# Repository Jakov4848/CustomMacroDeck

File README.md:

# MACRODECK

<!-- Add a photo of your finished Macropad here -->

This repository contains the hardware and software files for an open-source, programmable macropad keyboard based on the Arduino platform. Developed as a bachelor's thesis, this device allows users to store keyboard shortcuts directly on the hardware's memory, eliminating the need for complex PC software while improving daily workflow productivity.

## Features

- **Native USB HID Emulation:** Powered by an ATmega32U4 microcontroller with an integrated USB controller, meaning it works plug-and-play on any computer without extra drivers.
- **Mechanical Switch Matrix:** Features a 12-key grid with anti-ghosting diodes to prevent false key presses.
- **Hot-Swappable:** Utilizes hot-swap sockets for effortless mechanical switch replacement and testing.
- **Customizable RGB Lighting:** Addressable WS2812B NeoPixel LEDs provide per-key illumination with customizable static colors and dynamic effects.
- **On-Device Interface:** An integrated 0.96" I2C OLED display (SSD1306) and a rotary encoder allow users to navigate menus, select layers, and adjust PC volume directly from the device.
- **Persistent Memory:** Key bindings, macro steps, and layer names are permanently saved in the MCU's 1KB EEPROM.
- **Custom Real-Time Configuration Protocol:** Shortcuts can be reprogrammed in real-time via a serial UART interface using the Arduino IDE Serial Monitor or a Python script.
- **Custom Enclosure:** Designed with a 4-layer laser-cut acrylic (plexiglass) case.

---

## Hardware Bill of Materials (BOM)

The custom PCB was designed in KiCad. If you are assembling the board yourself, you will need the following components:

| Component                  | Description / Package                                            | Quantity |
| :------------------------- | :--------------------------------------------------------------- | :------- |
| **Microcontroller**        | ATmega32U4-AU (QFP-44 10x10)                                     | 1        |
| **USB Connector**          | USB 2.0 Type-C Receptacle 16-pin (SMD)                           | 1        |
| **Display**                | 0.96" OLED I2C SSD1306 (30x30)                                   | 1        |
| **Rotary Encoder**         | EC11 Rotary Switch (THT)                                         | 1        |
| **Mechanical Switches**    | Cherry MX Keyswitches (THT)                                      | 12       |
| **Hot-Swap Sockets**       | CPG151101S11-2 (SMD)                                             | 12       |
| **RGB Lighting LEDs**      | WS2812B NeoPixel LEDs                                            | 12       |
| **Anti-Ghosting Diodes**   | 1N4148W 75V 150mA (SOD-123)                                      | 12       |
| **Reset Switch**           | Tactile Switch 6.1x3.6mm (TS-1092S-B3D2-G)                       | 1        |
| **Crystal Oscillator**     | 16.000MHz SMD5032-2P (ABM3-16.000MHZ-D2Y-T)                      | 1        |
| **Protection**             | Schottky Diode 20V 500mA (MBR0520LT1G)                           | 1        |
| **Protection**             | Polymeric PTC Resettable Fuse 6V 500mA (SMD1206P050TF)           | 1        |
| **LED (Indication)**       | Blue 460nm LED (0603)                                            | 1        |
| **Resistors (0603)**       | 1kΩ (x1), 2.2kΩ (x2), 5.1kΩ (x2), 10kΩ (x2), 470Ω (x2), 22Ω (x2) | 11 Total |
| **Capacitors (0603/0805)** | 100nF (x6), 10uF (x1), 1uF (x1), 22pF (x2)                       | 10 Total |

---

## Building & Installation

1. **PCB & Enclosure:** The PCB manufacturing files are generated from KiCad. The enclosure is constructed from 4 layers of laser-cut black plexiglass.
2. **Bootloader:** A `USBasp` programmer is required to flash the initial bootloader to the ATmega32U4 chip using the ISP (In-System Programming) header.
3. **Firmware:** The firmware is written using the Arduino IDE. Once the bootloader is installed, you can flash updates directly via the USB-C port.

---

## Interface

The macropad operates on a Finite-State Machine with 8 distinct modes (states):

1. **NORMAL:** The primary working state. Scans for keypresses to execute macros and uses the rotary encoder to control PC volume.
2. **MAIN MENU:** Accessed by pressing the rotary encoder button. Allows navigation to other settings.
3. **LAYERS MENU:** Switch between different shortcut layers.
4. **LEDS MENU:** Access sub-menus for lighting.
5. **BRIGHTNESS MENU:** Adjust the intensity of the LED backlights.
6. **STATIC COLORS MENU:** Select a solid color for the keys.
7. **EFFECTS MENU:** Select dynamic RGB animations.
8. **PROG MODE (Programming):** Put the device into configuration mode to remap keys and rename layers via UART.

### Configuration Protocol (How to program macros?)

When the device is in `PROG MODE`, open the Arduino IDE Serial Monitor (or use a serial Python script) to send UART commands. Due to the 1KB EEPROM limit, each macro is restricted to a maximum of 10 sequential keystrokes.

- **To rename a layer**, send:
  `{{layer_id, layer_name}}`
- **To assign a shortcut to a key**, send:
  `<<layer_id, key_id, label, macro_steps>>`
- **To list all current shortcuts**, send:
  `?`

Whenever a programmed key is pressed in normal mode, a pop-up appears on the OLED display showing the executed shortcut (e.g., `CTRL+F`).

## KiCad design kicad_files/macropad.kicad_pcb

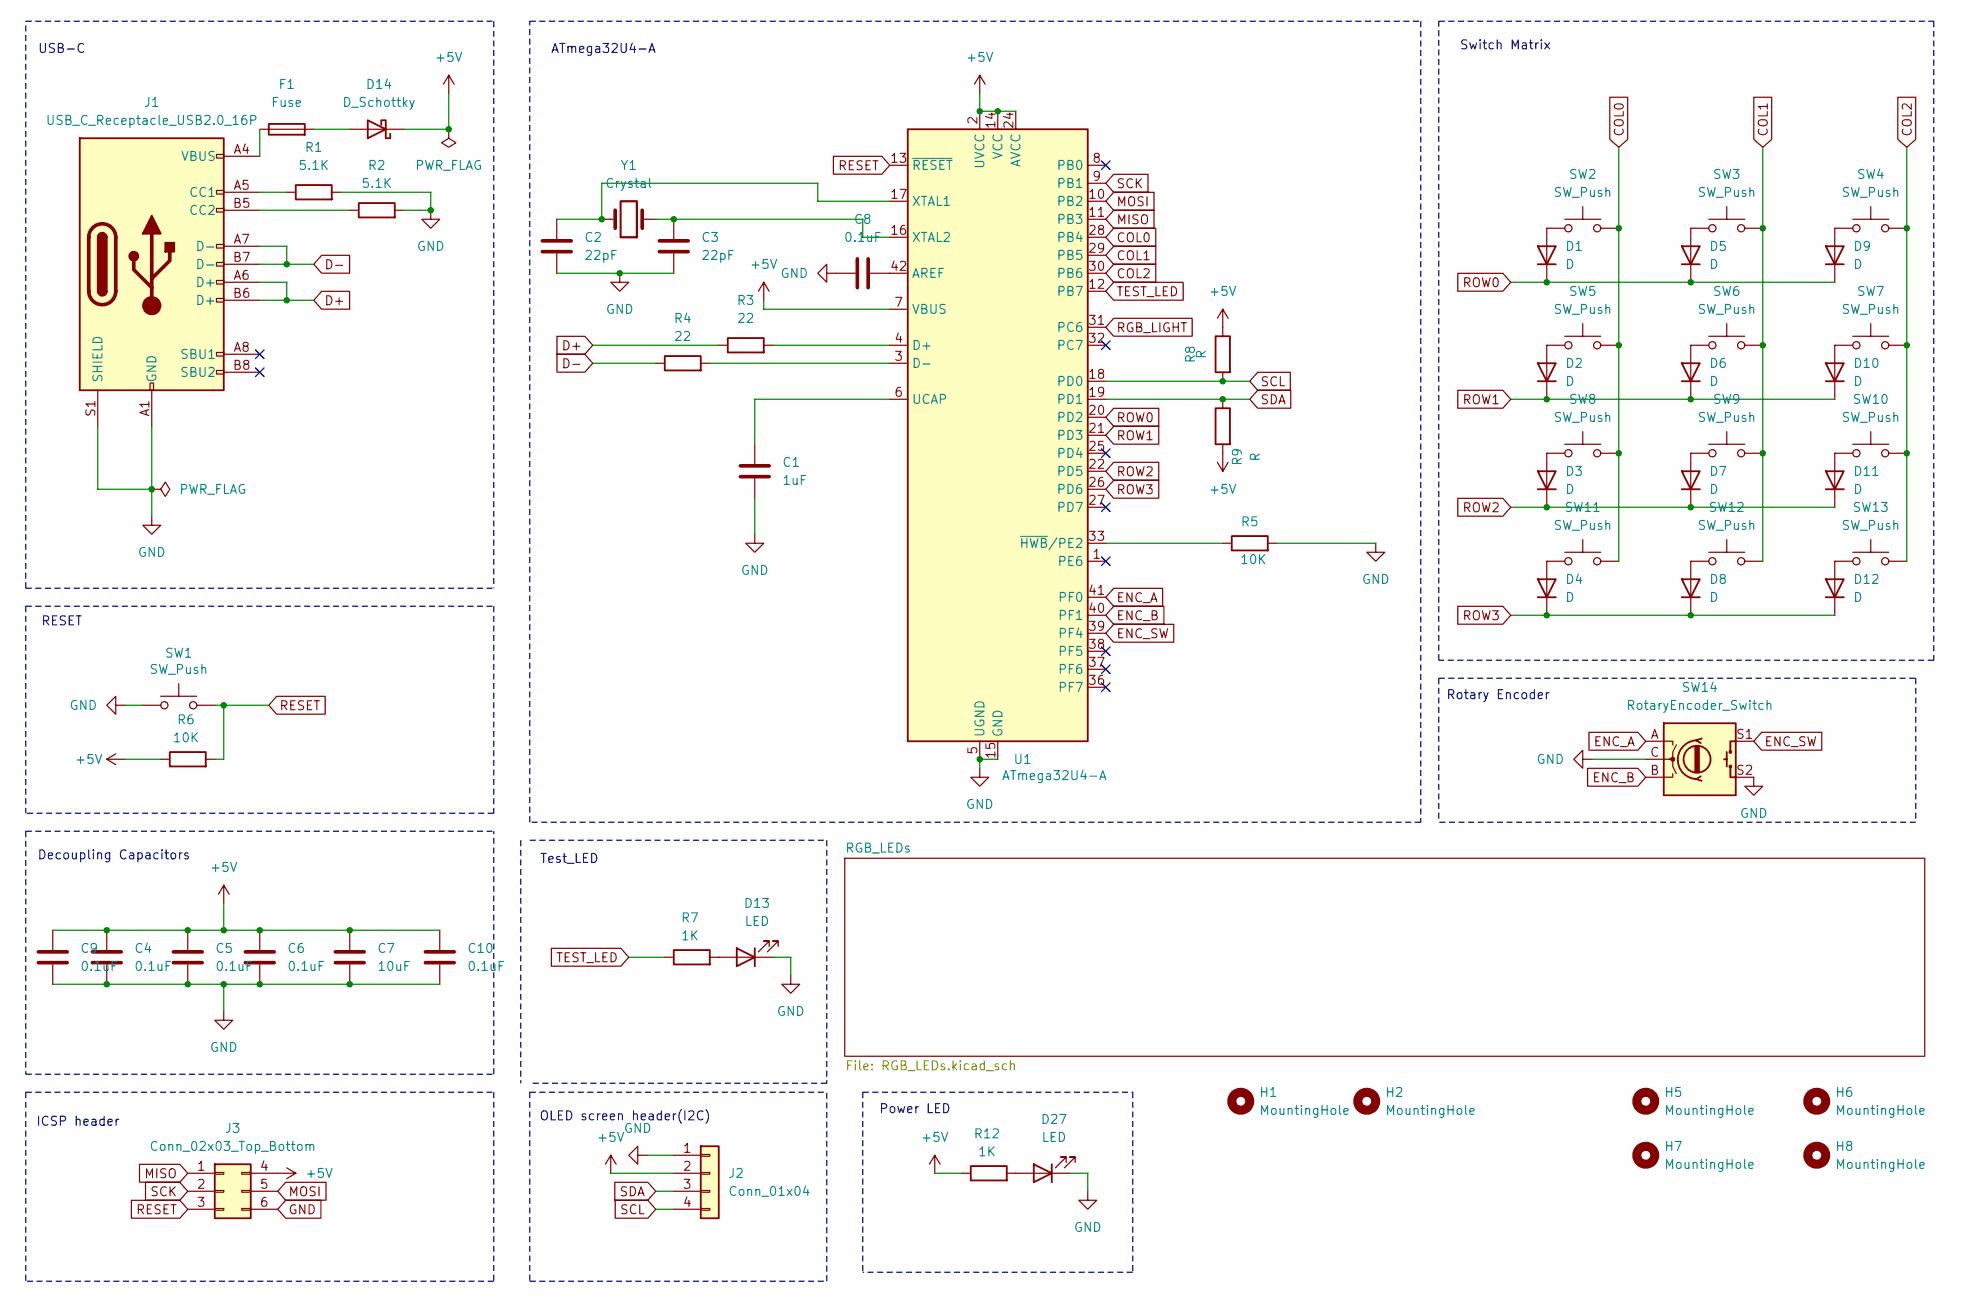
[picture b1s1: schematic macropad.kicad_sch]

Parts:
C1: 1uF; C_0603_1608Metric_Pad1.08x0.95mm_HandSolder
C2, C3: 22pF; C_0603_1608Metric_Pad1.08x0.95mm_HandSolder
C4, C5, C6, C8, C9, C10: 0.1uF; C_0603_1608Metric_Pad1.08x0.95mm_HandSolder
C7: 10uF; C_0805_2012Metric_Pad1.18x1.45mm_HandSolder
D1, D2, D3, D4, D5, D6, D7, D8, D9, D10, D11, D12: D; D_SOD-123
D13, D27: LED; LED_0603_1608Metric_Pad1.05x0.95mm_HandSolder
D14: D_Schottky; D_SOD-123
F1: Fuse; Fuse_1206_3216Metric_Pad1.42x1.75mm_HandSolder
H1, H2: MountingHole; MountingHole_3.2mm_M3
H5, H6, H7, H8: MountingHole; MountingHole_2.2mm_M2
J1: USB_C_Receptacle_USB2.0_16P; USB_C_Receptacle_HRO_TYPE-C-31-M-12
J2: Conn_01x04; PinSocket_1x04_P2.54mm_Vertical
J3: Conn_02x03_Top_Bottom; PinHeader_2x03_P2.54mm_Vertical
R1, R2: 5.1K; R_0603_1608Metric_Pad0.98x0.95mm_HandSolder
R3, R4: 22; R_0603_1608Metric_Pad0.98x0.95mm_HandSolder
R5, R6: 10K; R_0603_1608Metric_Pad0.98x0.95mm_HandSolder
R7, R12: 1K; R_0603_1608Metric_Pad0.98x0.95mm_HandSolder
R8, R9: R; R_0603_1608Metric_Pad0.98x0.95mm_HandSolder
SW1: SW_Push; SW_SPST_CK_RS282G05A3
SW2, SW3, SW4, SW5, SW6, SW7, SW8, SW9, SW10, SW11, SW12, SW13: SW_Push; SW_Hotswap_Kailh_MX_1.00u
SW14: RotaryEncoder_Switch; RotaryEncoder_Alps_EC11E-Switch_Vertical_H20mm_MountingHoles
U1: ATmega32U4-A; TQFP-44_10x10mm_P0.8mm
Y1: Crystal; Crystal_SMD_Abracon_ABM3-2Pin_5.0x3.2mm_HandSoldering

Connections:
+5V: C4.1, C5.1, C6.1, C7.1, C9.1, C10.1, D14.1 (K), J2.2, J3.4, R6.1, R8.1, R9.2, R12.1, U1.2 (UVCC), U1.7 (VBUS), U1.14 (VCC), U1.24 (AVCC), U1.34 (VCC), U1.44 (AVCC); also elsewhere on the board
COL0: SW2.2, SW5.2, SW8.2, SW11.2, U1.28 (PB4)
COL1: SW3.2, SW6.2, SW9.2, SW12.2, U1.29 (PB5)
COL2: SW4.2, SW7.2, SW10.2, SW13.2, U1.30 (PB6)
D+: J1.A6 (D+), J1.B6 (D+), R3.1
D-: J1.A7 (D-), J1.B7 (D-), R4.1
ENC_A: SW14.A, U1.41 (PF0)
ENC_B: SW14.B, U1.40 (PF1)
ENC_SW: SW14.S1, U1.39 (PF4)
GND: C1.2, C2.2, C3.2, C4.2, C5.2, C6.2, C7.2, C8.1, C9.2, C10.2, D13.1 (K), D27.1 (K), J1.A1 (GND), J1.A12 (GND), J1.B1 (GND), J1.B12 (GND), J1.S1 (SHIELD), J2.1, J3.6, R1.2, R2.2, R5.2, SW1.1, SW14.C, SW14.S2, U1.5 (UGND), U1.15 (GND), U1.23 (GND), U1.35 (GND), U1.43 (GND); also elsewhere on the board
MISO: J3.1, U1.11 (PB3)
MOSI: J3.5, U1.10 (PB2)
unnamed: D1.2 (A), SW2.1
unnamed: D2.2 (A), SW5.1
unnamed: D3.2 (A), SW8.1
unnamed: D4.2 (A), SW11.1
unnamed: D5.2 (A), SW3.1
unnamed: D6.2 (A), SW6.1
unnamed: D7.2 (A), SW9.1
unnamed: D8.2 (A), SW12.1
unnamed: D9.2 (A), SW4.1
unnamed: D10.2 (A), SW7.1
unnamed: D11.2 (A), SW10.1
unnamed: D12.2 (A), SW13.1
unnamed: D13.2 (A), R7.2
unnamed: D14.2 (A), F1.2
unnamed: D27.2 (A), R12.2
unnamed: F1.1, J1.A4 (VBUS), J1.A9 (VBUS), J1.B4 (VBUS), J1.B9 (VBUS)
unnamed: J1.A5 (CC1), R1.1
unnamed: J1.B5 (CC2), R2.1
unnamed: C8.2, U1.42 (AREF)
unnamed: R3.2, U1.4 (D+)
unnamed: R4.2, U1.3 (D-)
unnamed: C1.1, U1.6 (UCAP)
unnamed: C2.1, U1.17 (XTAL1), Y1.2
unnamed: C3.1, U1.16 (XTAL2), Y1.1
unnamed: R5.1, U1.33 (~HWB/PE2)
RESET: J3.3, R6.2, SW1.2, U1.13 (~RESET)
RGB_LIGHT: U1.31 (PC6); also elsewhere on the board
ROW0: D1.1 (K), D5.1 (K), D9.1 (K), U1.20 (PD2)
ROW1: D2.1 (K), D6.1 (K), D10.1 (K), U1.21 (PD3)
ROW2: D3.1 (K), D7.1 (K), D11.1 (K), U1.22 (PD5)
ROW3: D4.1 (K), D8.1 (K), D12.1 (K), U1.26 (PD6)
SCK: J3.2, U1.9 (PB1)
SCL: J2.4, R8.2, U1.18 (PD0)
SDA: J2.3, R9.1, U1.19 (PD1)
TEST_LED: R7.1, U1.12 (PB7)

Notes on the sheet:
RESET
Power LED
Rotary Encoder
ICSP header
Test_LED
Switch Matrix
USB-C
ATmega32U4-A
Decoupling Capacitors
OLED screen header(I2C)

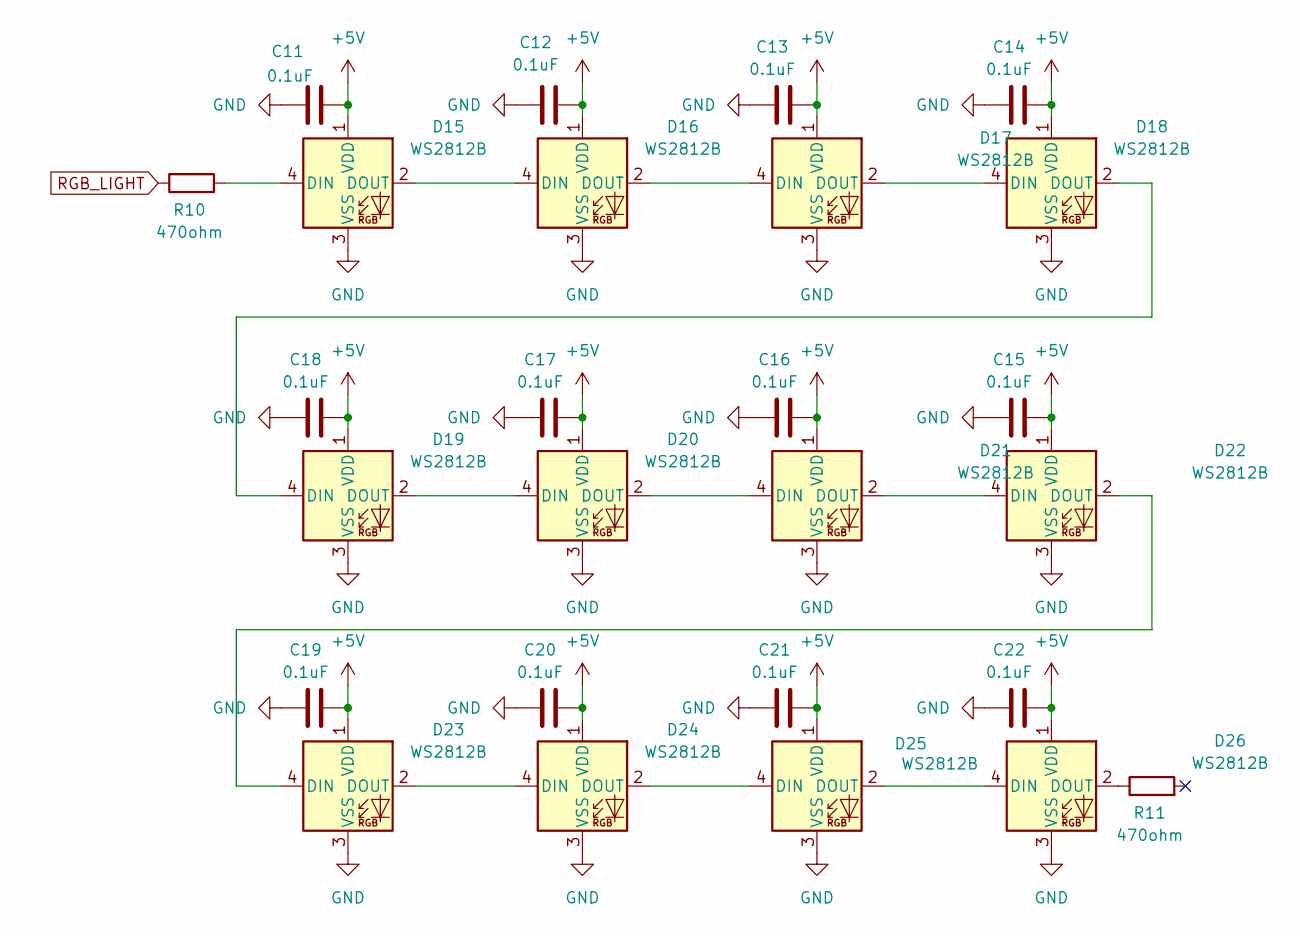
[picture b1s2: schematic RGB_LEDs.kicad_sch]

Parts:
C11, C12, C13, C14, C15, C16, C17, C18, C19, C20, C21, C22: 0.1uF; C_0603_1608Metric_Pad1.08x0.95mm_HandSolder
D15, D16, D17, D18, D19, D20, D21, D22, D23, D24, D25, D26: WS2812B; LED_WS2812B-2020_PLCC4_2.0x2.0mm
R10, R11: 470ohm; R_0603_1608Metric_Pad0.98x0.95mm_HandSolder

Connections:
+5V: C11.2, C12.2, C13.2, C14.2, C15.2, C16.2, C17.2, C18.2, C19.2, C20.2, C21.2, C22.2, D15.1 (VDD), D16.1 (VDD), D17.1 (VDD), D18.1 (VDD), D19.1 (VDD), D20.1 (VDD), D21.1 (VDD), D22.1 (VDD), D23.1 (VDD), D24.1 (VDD), D25.1 (VDD), D26.1 (VDD); also elsewhere on the board
GND: C11.1, C12.1, C13.1, C14.1, C15.1, C16.1, C17.1, C18.1, C19.1, C20.1, C21.1, C22.1, D15.3 (VSS), D16.3 (VSS), D17.3 (VSS), D18.3 (VSS), D19.3 (VSS), D20.3 (VSS), D21.3 (VSS), D22.3 (VSS), D23.3 (VSS), D24.3 (VSS), D25.3 (VSS), D26.3 (VSS); also elsewhere on the board
unnamed: D15.4 (DIN), R10.2
unnamed: D15.2 (DOUT), D16.4 (DIN)
unnamed: D16.2 (DOUT), D17.4 (DIN)
unnamed: D17.2 (DOUT), D18.4 (DIN)
unnamed: D18.2 (DOUT), D19.4 (DIN)
unnamed: D19.2 (DOUT), D20.4 (DIN)
unnamed: D20.2 (DOUT), D21.4 (DIN)
unnamed: D21.2 (DOUT), D22.4 (DIN)
unnamed: D22.2 (DOUT), D23.4 (DIN)
unnamed: D23.2 (DOUT), D24.4 (DIN)
unnamed: D24.2 (DOUT), D25.4 (DIN)
unnamed: D25.2 (DOUT), D26.4 (DIN)
unnamed: D26.2 (DOUT), R11.1
RGB_LIGHT: R10.1; also elsewhere on the board

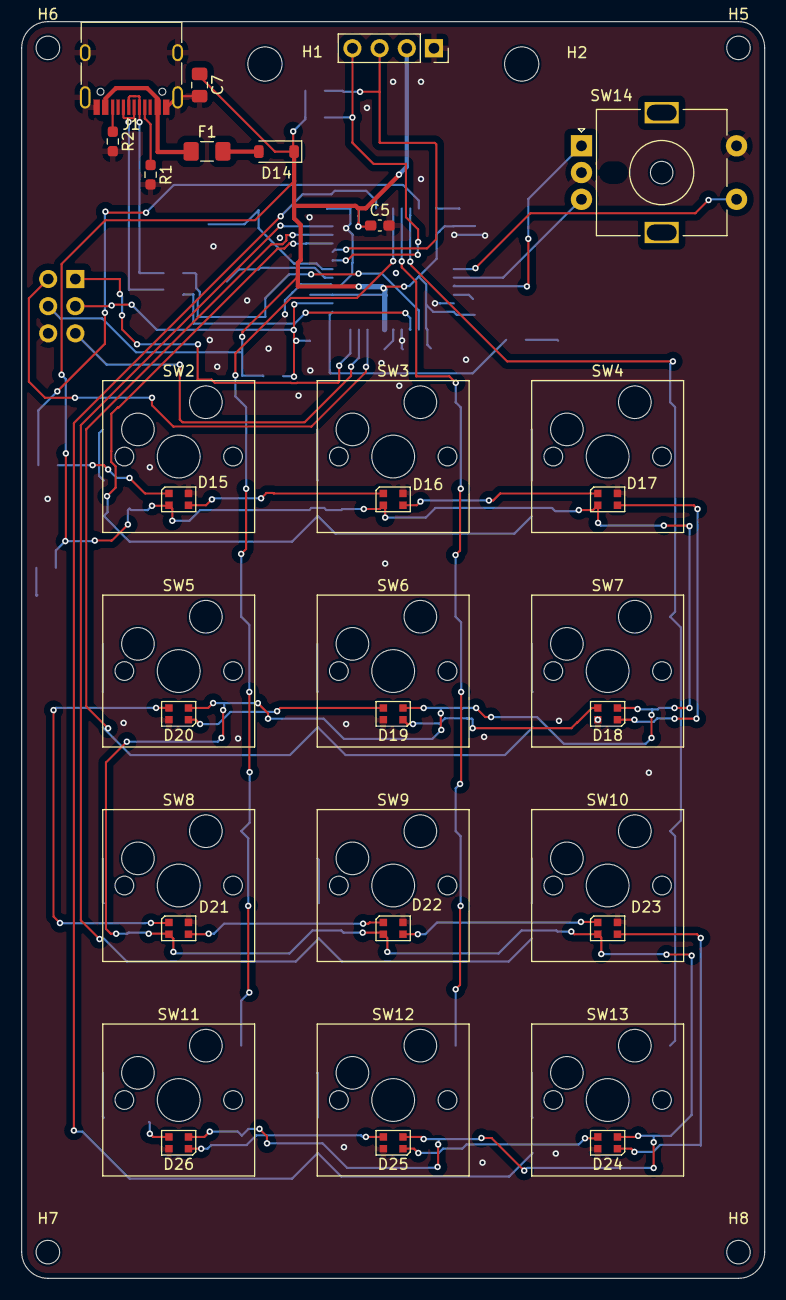
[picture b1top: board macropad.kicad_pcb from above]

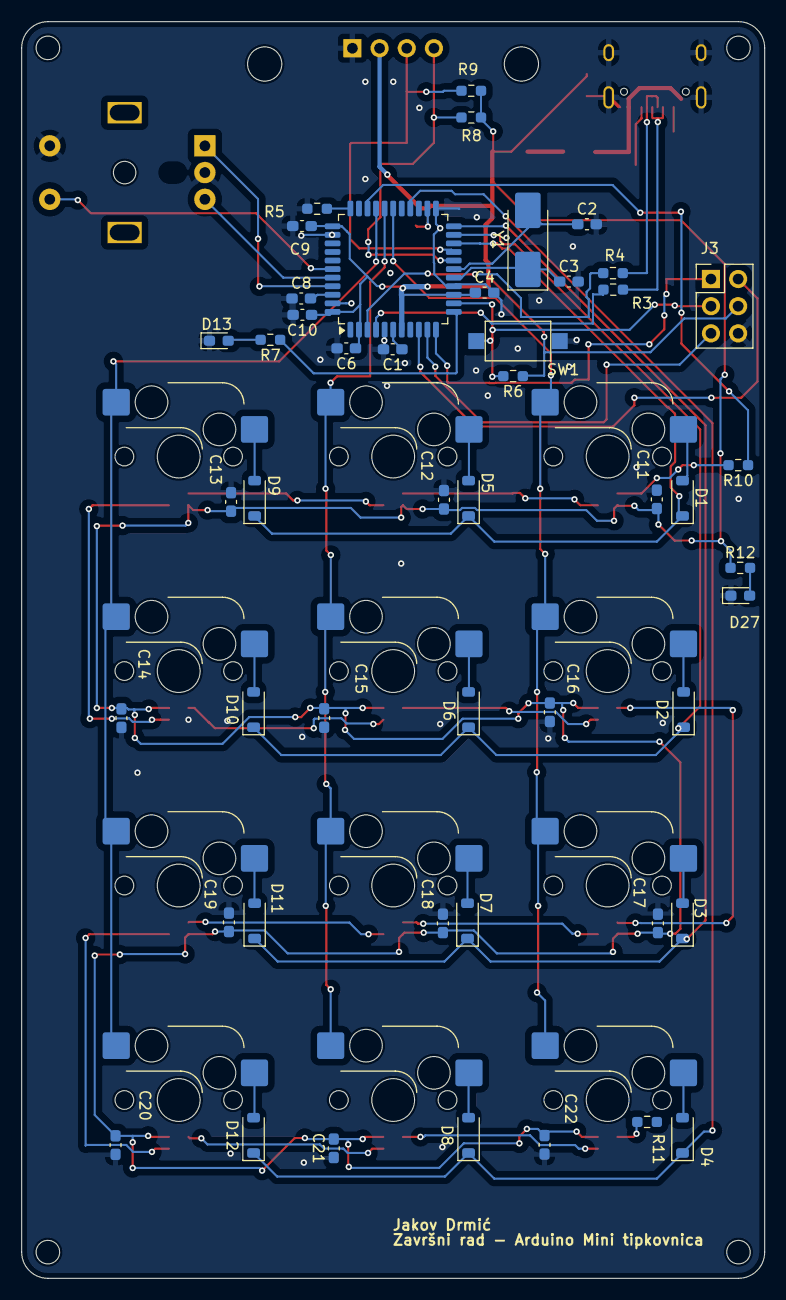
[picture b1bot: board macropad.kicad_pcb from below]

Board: 2 copper layers, 69.5 x 117.5 mm, 87 parts (48 on the bottom side), 60 nets.

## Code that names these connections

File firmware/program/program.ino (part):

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#define STATE_EFFECTS_MENU 7

//  Rotary encoder
#define ENC_A A5
#define ENC_B A4
#define ENC_SW A3


Adafruit_SSD1306 display(SCREEN_WIDTH, SCREEN_HEIGHT, &Wire, OLED_RESET);
Adafruit_NeoPixel pixels(NUMPIXELS, LED_PIN, NEO_GRB + NEO_KHZ800);

int rowPins[NUM_ROWS] = {0, 1, 30, 12};  // PD2=0, PD3=1, PD5=30, PD6=12
int colPins[NUM_COLS] = {8, 9, 10};      // PB4=8, PB5=9, PB6=10

int currentScreenState = STATE_NORMAL; 
int menuIndex = 0; 
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  Serial.begin(SERIAL_BAUD); 

  // encoder pin config
  pinMode(ENC_A, INPUT_PULLUP);
  pinMode(ENC_B, INPUT_PULLUP);
  pinMode(ENC_SW, INPUT_PULLUP);
  lastEncoderStateA = digitalRead(ENC_A);

  // switch matrix config
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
